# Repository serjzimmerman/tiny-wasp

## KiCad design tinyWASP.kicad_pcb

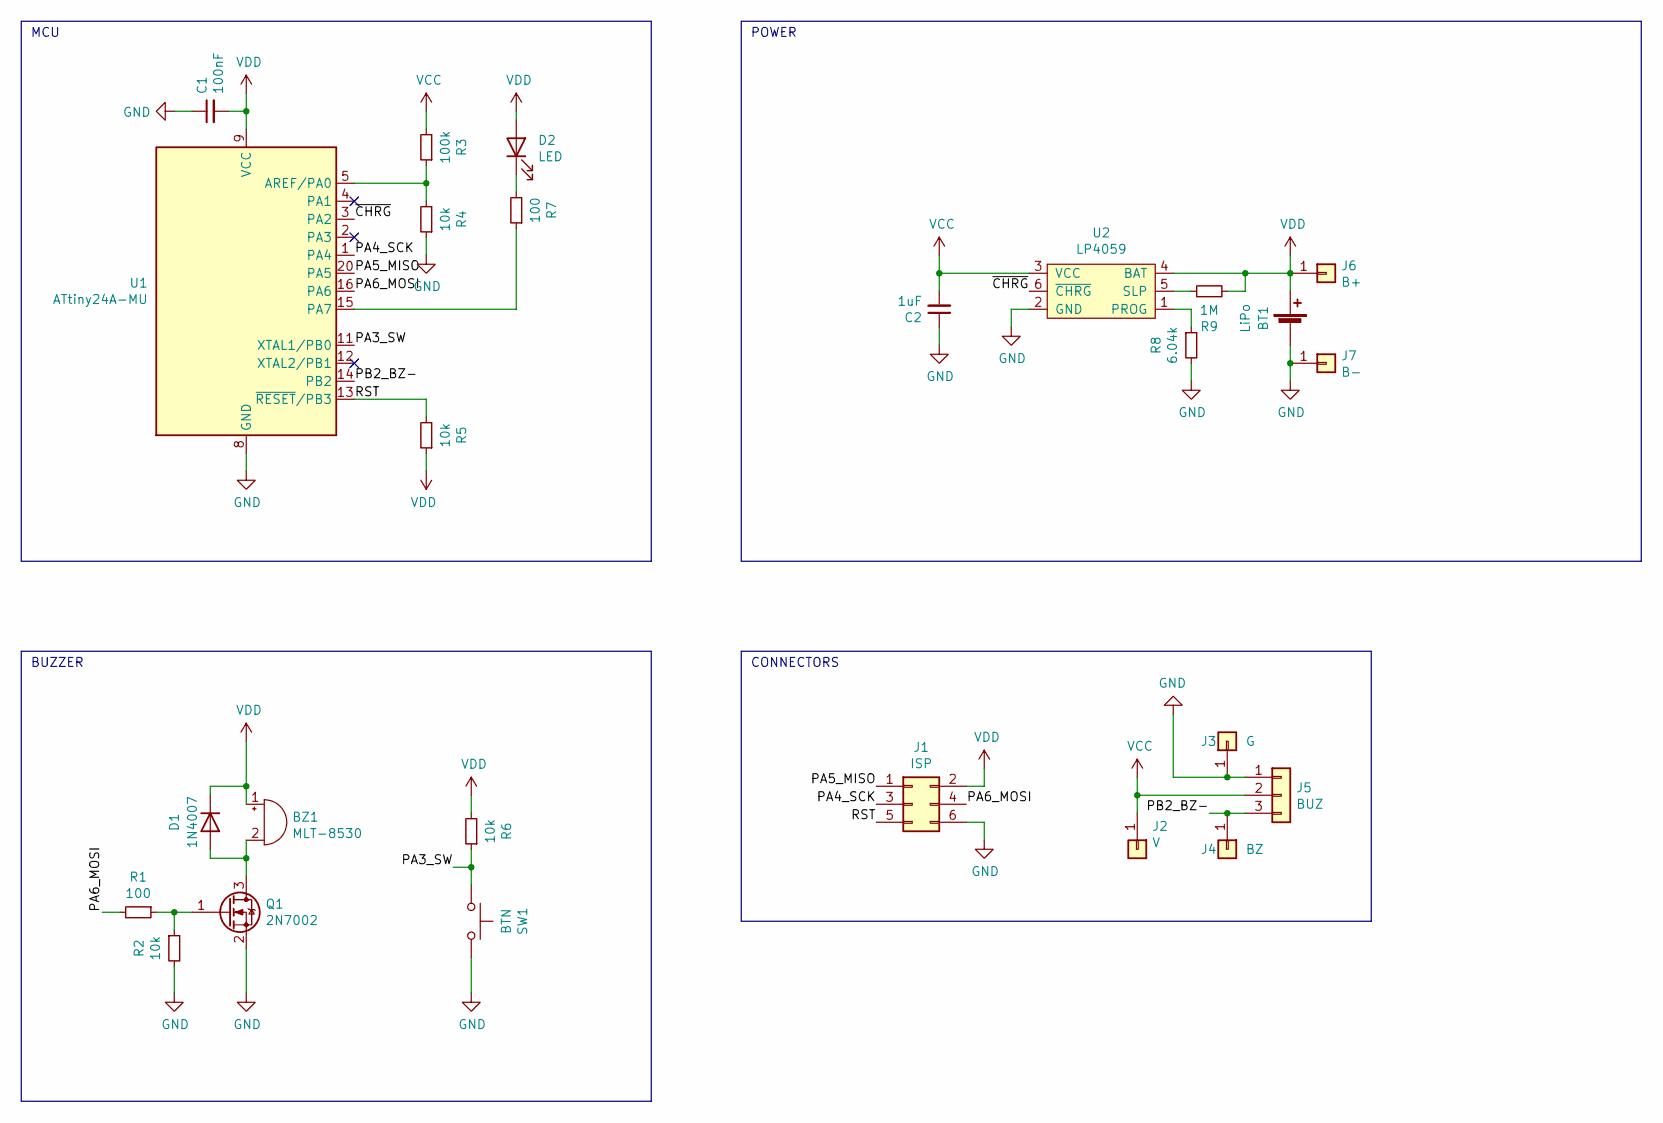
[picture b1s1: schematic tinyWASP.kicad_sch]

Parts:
BT1: LiPo
BZ1: MLT-8530; MagneticBuzzer_CUI_CMT-8504-100-SMT; LCSC C94599
C1: 100nF; C_0402_1005Metric; LCSC C60474
C2: 1uF; C_0402_1005Metric; LCSC C92755
D1: 1N4007; D_SOD-323; LCSC C193404
D2: LED; LED_0603_1608Metric; LCSC C72041
J1: ISP; PinHeader_2x03_P1.27mm_Vertical_SMD; LCSC C59981
J2: V; TestPoint_Pad_1.0x1.0mm
J3: G; TestPoint_Pad_1.0x1.0mm
J4: BZ; TestPoint_Pad_1.0x1.0mm
J5: BUZ; JST_SH_SM03B-SRSS-TB_1x03-1MP_P1.00mm_Horizontal; LCSC C541845
J6: B+; TestPoint_Pad_D1.0mm
J7: B-; TestPoint_Pad_1.0x1.0mm
Q1: 2N7002; SOT-23; LCSC C65189
R1, R7: 100; R_0402_1005Metric; LCSC C106233
R2, R4, R5, R6: 10k; R_0402_1005Metric; LCSC C60489
R3: 100k; R_0402_1005Metric; LCSC C106234
R8: 6.04k; R_0402_1005Metric; LCSC C25913
R9: 1M; R_0402_1005Metric; LCSC C26087
SW1: BTN; SW_Push_SPST_NO_Alps_SKRK; LCSC C557591
U1: ATtiny24A-MU; QFN-20-1EP_4x4mm_P0.5mm_EP2.6x2.6mm; LCSC C19354
U2: LP4059; DFN-6-1EP_2x2mm_P0.65mm_EP1x1.6mm; LCSC C517025

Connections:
/PA3_SW: R6.1, SW1.1, U1.11 (XTAL1/PB0)
/PA4_SCK: J1.3, U1.1 (PA4)
/PA5_MISO: J1.1, U1.20 (PA5)
/PA6_MOSI: J1.4, R1.2, U1.16 (PA6)
/PB2_BZ-: J4.1, J5.3, U1.14 (PB2)
/RST: J1.5, R5.2, U1.13 (~RESET/PB3)
/~CHRG: U1.3 (PA2), U2.6 (~CHRG)
GND: BT1.2 (-), C1.1, C2.1, J1.6, J3.1, J5.1, J7.1, Q1.2 (S), R2.2, R4.1, R8.2, SW1.2, U1.8 (GND), U1.21 (GND), U2.2 (GND)
unnamed: BZ1.2 (+), D1.2 (A), Q1.3 (D)
unnamed: D2.1 (K), R7.2
unnamed: Q1.1 (G), R1.1, R2.1
unnamed: R3.1, R4.2, U1.5 (AREF/PA0)
unnamed: R7.1, U1.15 (PA7)
unnamed: R8.1, U2.1 (PROG)
unnamed: R9.1, U2.5 (SLP)
VCC: C2.2, J2.1, J5.2, R3.2, U2.3 (VCC)
VDD: BT1.1 (+), BZ1.1 (-), C1.2, D1.1 (K), D2.2 (A), J1.2, J6.1, R5.1, R6.2, R9.2, U1.9 (VCC), U2.4 (BAT)

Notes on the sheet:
POWER
MCU
BUZZER
CONNECTORS

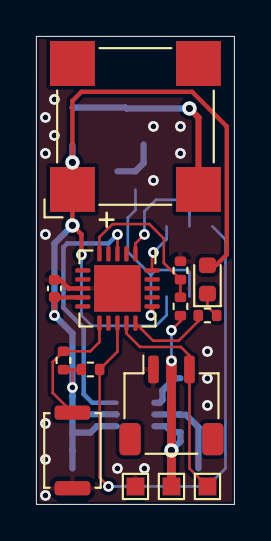
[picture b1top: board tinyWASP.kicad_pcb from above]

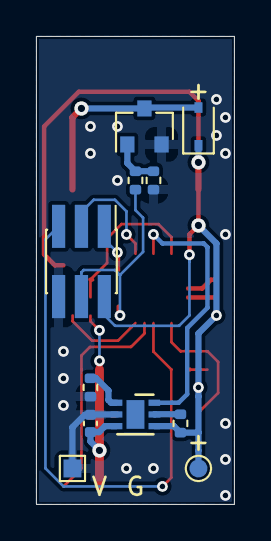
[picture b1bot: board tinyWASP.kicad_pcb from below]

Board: 2 copper layers, 11.0 x 26.0 mm, 25 parts (11 on the bottom side), 17 nets.

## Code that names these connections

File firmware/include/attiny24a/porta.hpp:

/** ----------------------------------------------------------------------------'
 * "THE BEER-WARE LICENSE" (Revision 42):'
 * <tsimmerman.ss@phystech.edu> wrote this file.  As long'
 * as you retain this notice you can do whatever you want with this stuff. If we'
 * meet some day, and you think this stuff is worth it, you can buy me a beer in'
 * return.'
 * ----------------------------------------------------------------------------'
 */

#pragma once

#include "avrcpp/register.hpp"

namespace avrcpp::attiny24a::mporta
{

// Port A Data Direction Register
using ddra_register = avrcpp::register_wrapper<0x3a, 1, avrcpp::read_write_flag>;

namespace ddra_fields
{

// Pin A0
constexpr auto pa0 = avrcpp::register_field<ddra_register, 0, 1>{ 1 };

// Pin A1
constexpr auto pa1 = avrcpp::register_field<ddra_register, 1, 1>{ 1 };

// Pin A2
constexpr auto pa2 = avrcpp::register_field<ddra_register, 2, 1>{ 1 };

// Pin A3
constexpr auto pa3 = avrcpp::register_field<ddra_register, 3, 1>{ 1 };

// Pin A4
constexpr auto pa4 = avrcpp::register_field<ddra_register, 4, 1>{ 1 };

// Pin A5
constexpr auto pa5 = avrcpp::register_field<ddra_register, 5, 1>{ 1 };

// Pin A6
constexpr auto pa6 = avrcpp::register_field<ddra_register, 6, 1>{ 1 };

// Pin A7
constexpr auto pa7 = avrcpp::register_field<ddra_register, 7, 1>{ 1 };

} // namespace ddra_fields

constexpr auto ddra = ddra_register{};

// Port A Input Pins
using pina_register = avrcpp::register_wrapper<0x39, 1, avrcpp::read_write_flag>;

namespace pina_fields
{

// Pin A0
constexpr auto pa0 = avrcpp::register_field<pina_register, 0, 1>{ 1 };

// Pin A1
constexpr auto pa1 = avrcpp::register_field<pina_register, 1, 1>{ 1 };

// Pin A2
constexpr auto pa2 = avrcpp::register_field<pina_register, 2, 1>{ 1 };

// Pin A3
constexpr auto pa3 = avrcpp::register_field<pina_register, 3, 1>{ 1 };

// Pin A4
constexpr auto pa4 = avrcpp::register_field<pina_register, 4, 1>{ 1 };

// Pin A5
constexpr auto pa5 = avrcpp::register_field<pina_register, 5, 1>{ 1 };

// Pin A6
constexpr auto pa6 = avrcpp::register_field<pina_register, 6, 1>{ 1 };

// Pin A7
constexpr auto pa7 = avrcpp::register_field<pina_register, 7, 1>{ 1 };

} // namespace pina_fields

constexpr auto pina = pina_register{};

// Port A Data Register
using porta_register = avrcpp::register_wrapper<0x3b, 1, avrcpp::read_write_flag>;

namespace porta_fields
{

// Pin A0
constexpr auto pa0 = avrcpp::register_field<porta_register, 0, 1>{ 1 };

// Pin A1
constexpr auto pa1 = avrcpp::register_field<porta_register, 1, 1>{ 1 };

// Pin A2
constexpr auto pa2 = avrcpp::register_field<porta_register, 2, 1>{ 1 };

// Pin A3
constexpr auto pa3 = avrcpp::register_field<porta_register, 3, 1>{ 1 };

// Pin A4
constexpr auto pa4 = avrcpp::register_field<porta_register, 4, 1>{ 1 };

// Pin A5
constexpr auto pa5 = avrcpp::register_field<porta_register, 5, 1>{ 1 };

// Pin A6
constexpr auto pa6 = avrcpp::register_field<porta_register, 6, 1>{ 1 };

// Pin A7
constexpr auto pa7 = avrcpp::register_field<porta_register, 7, 1>{ 1 };

} // namespace porta_fields

constexpr auto porta = porta_register{};

} // namespace avrcpp::attiny24a::mporta

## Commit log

2024-08-31 feat: added interactive bom
2024-08-31 feat: fixed .kicad_pcb
2024-08-31 feat: first fommit
2024-08-31 feat: added production files
2024-08-31 chore: update to newer kicad version
2024-08-31 feat(firmware): add led wrapper
2024-08-31 docs: remove autogenerated readmes
2024-08-31 misc: test more includes
2024-08-31 fix: rework values
2024-08-31 feat(firmware): configure timer
2024-08-31 docs: add images
2024-08-31 feat(firmware): generate c++ wrapper code with python
2024-08-31 fix: rename library folder and update symbol lib format
2024-08-31 fix: change naming, add .gitignore
2024-08-31 feat(firmware): calculate timer prescalers at compile time
2024-08-31 feat(firmware): user defined literal for voltage
2024-08-31 feat(firmware): add enable/disable functions
2024-08-31 feat(firmware): disable interrupts for button in most states
2024-08-31 feat(firmware): working main application logic
2024-08-31 feat(firmware): fixed point math for adc
2024-08-31 feat(firmware): working triple press for transition
2024-08-31 feat(firmware): working prototype version
2024-08-31 feat(firmware): simple adc
2024-08-31 feat(firmware): eeprom variables
2024-08-31 feat(firmware): outline of the basic program logic
